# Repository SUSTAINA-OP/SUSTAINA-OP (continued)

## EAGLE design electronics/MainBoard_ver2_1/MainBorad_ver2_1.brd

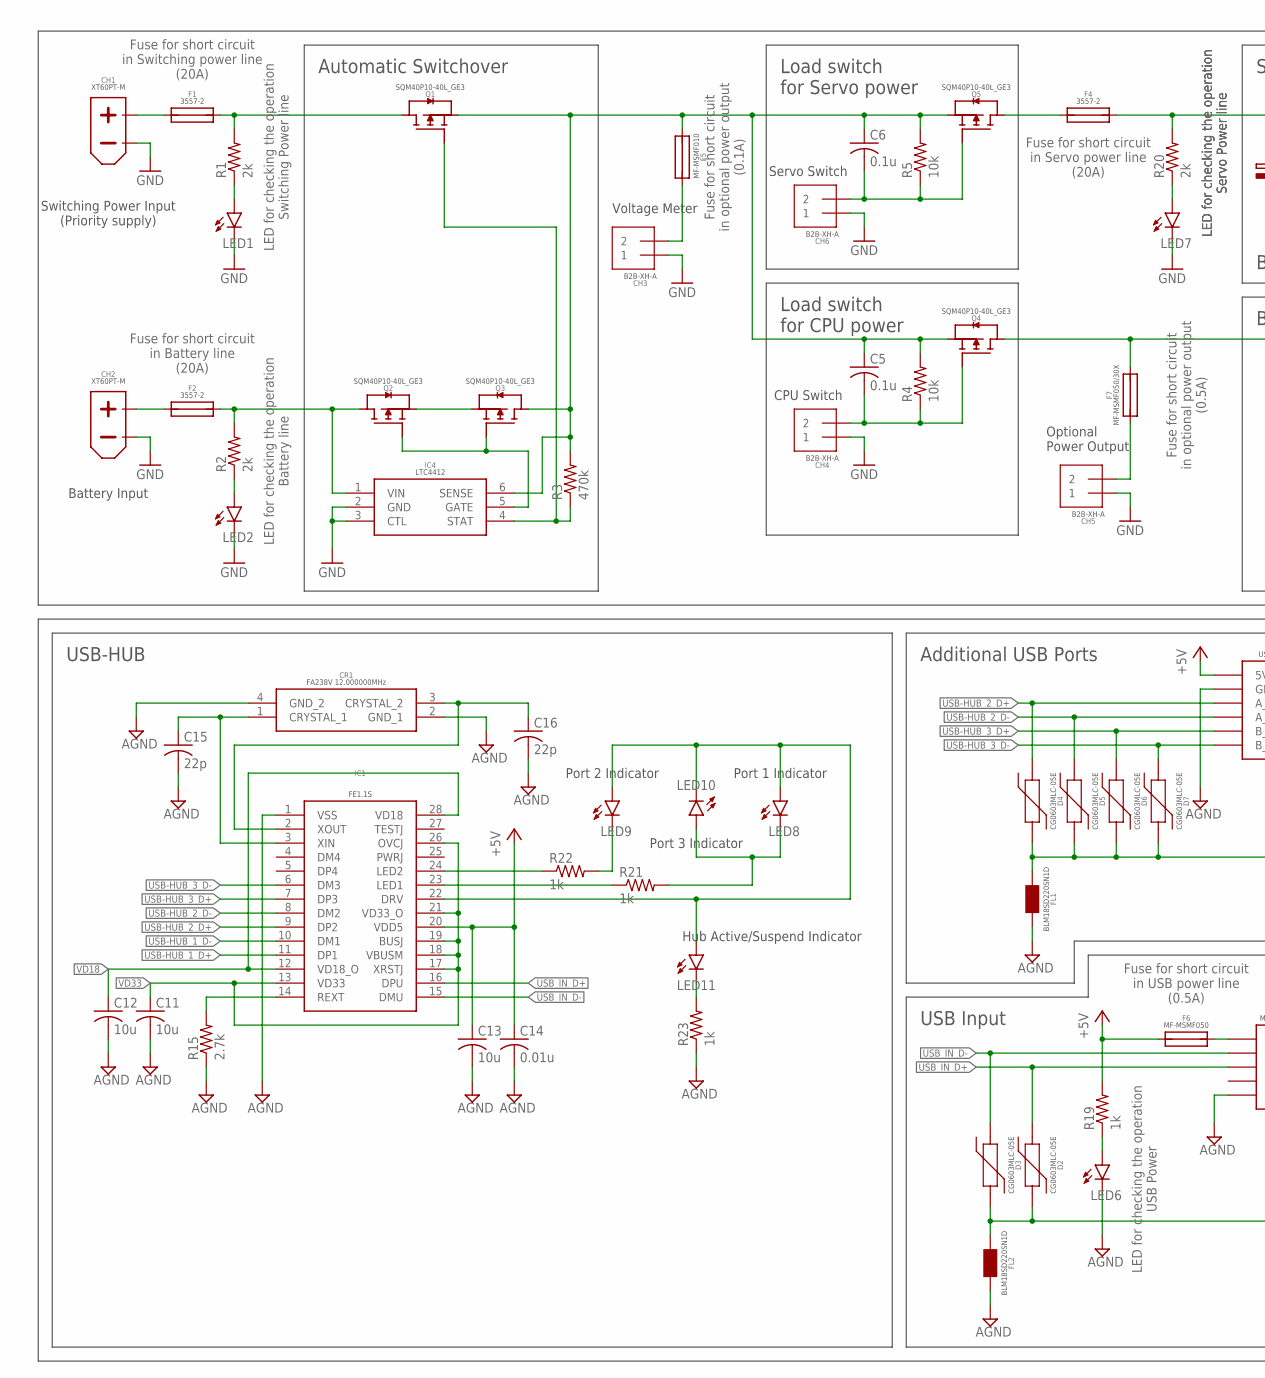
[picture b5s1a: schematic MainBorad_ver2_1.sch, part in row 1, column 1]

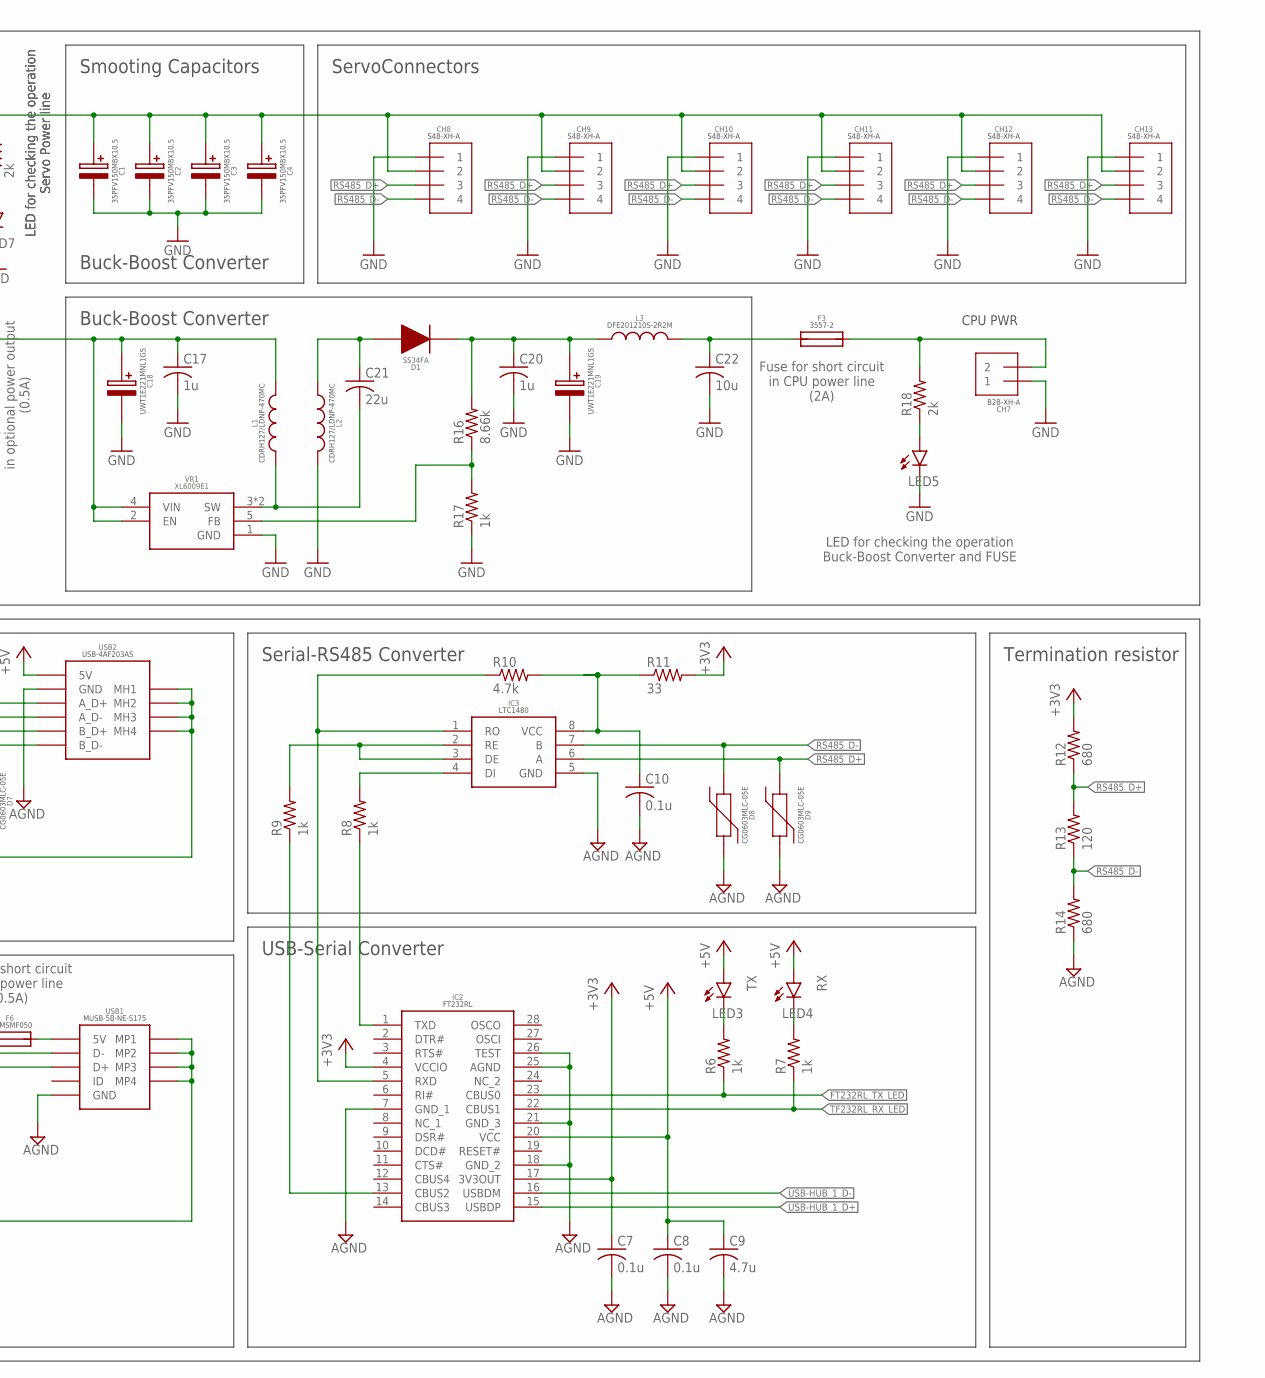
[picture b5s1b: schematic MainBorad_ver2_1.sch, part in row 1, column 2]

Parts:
C1, C2, C3, C4: 35PFV150M8X10.5
C5, C6, C7, C8, C10: 0.1u; C0603
C9: 4.7u; C0603
C11, C12, C13, C22: 10u; C0603
C14: 0.01u; C0603
C15, C16: 22p; C0603
C17, C20: 1u; C0603
C18, C19: UWT1E221MNL1GS
C21: 22u; C2012
CH1, CH2: XT60PT-M
CH3, CH4, CH5, CH6, CH7: B2B-XH-A
CH8, CH9, CH10, CH11, CH12, CH13: S4B-XH-A
CR1: FA238V_12.000000MHZ; FA238V
D1: SS34FA
D2, D3, D4, D5, D6, D7, D8, D9: CG0603MLC-05E
F1, F2, F3, F4: 3557-2
F5: MF-MSMF010
F6: MF-MSMF050
F7: MF-MSMF050/30X; MF-MSMF050
FL1, FL2: BLM18SD220SN1D
IC1: FE1.1S
IC2: FT232RL
IC3: LTC1480
IC4: LTC4412
L1, L2: CDRH127/LDNP-470MC; CDRH127/LDNP
L3: DFE201210S-2R2M; DFE201210S
LED1, LED2, LED3, LED4, LED5, LED6, LED7, LED8, LED9, LED10, LED11: LEDSML0603; SML0603
Q1, Q2, Q3, Q4, Q5: SQM40P10-40L_GE3; TO-252-3
R1, R2, R18, R20: 2k; R0603
R3: 470k; R0603
R4, R5: 10k; R0603
R6, R7, R8, R9, R17, R19, R21, R22, R23: 1k; R0603
R10: 4.7k; R0603
R11: 33; R0603
R12, R14: 680; R0603
R13: 120; R0603
R15: 2.7k; R0603
R16: 8.66k; R0603
USB1: MINI_USB_5P_B_TYPE
USB2: USB_4P_A_TYPE_X2
VR1: XL6009E1; TO263-5L

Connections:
+3V3: C7.1, IC2.4 (VCCIO), IC2.17 (3V3OUT), R11.2, R12.2
+5V: C8.1, C9.1, C13.1, C14.1, F6.1, IC1.20 (VDD5), IC2.20 (VCC), LED3.A, LED4.A, R19.2, USB2.4 (5V), USB2.8 (5V)
AGND: C7.2, C8.2, C9.2, C10.2, C11.2, C12.2, C13.2, C14.2, C15.2, C16.2, CR1.2 (GND_1), CR1.4 (GND_2), D8.2, D9.2, FL1.2, FL2.2, IC1.1 (VSS), IC2.7 (GND_1), IC2.18 (GND_2), IC2.21 (GND_3), IC2.25 (AGND), IC2.26 (TEST), IC3.5 (GND), LED6.C, R14.1, R15.1, R23.1, USB1.5 (GND), USB2.1 (GND), USB2.5 (GND)
A_DIODE_DCDC: C19.+, C20.1, D1.1, L3.1, R16.2
A_FUSE_BATT: F2.3 (2), F2.4 (2), IC4.1 (VIN), Q2.4 (D), R2.2
A_FUSE_DCDC: CH7.2, F3.3 (2), F3.4 (2), R18.2
A_FUSE_METER: CH3.2, F5.2
A_FUSE_PWR: F1.3 (2), F1.4 (2), Q1.4 (D), R1.2
A_FUSE_SERVO: C1.+, C2.+, C3.+, C4.+, CH8.2, CH9.2, CH10.2, CH11.2, CH12.2, CH13.2, F4.3 (2), F4.4 (2), R20.2
B_DIODE_DCDC: C21.1, D1.2, L2.1
B_FUSE_BATT: CH2.+, F2.1, F2.2 (1)
B_FUSE_DCDC: C22.1, F3.1, F3.2 (1), L3.2
B_FUSE_PWR: CH1.+, F1.1, F1.2 (1)
B_FUSE_SERVO: F4.1, F4.2 (1), Q5.4 (D)
B_FUSE_USB_MINI_B: F6.2, USB1.1 (5V)
B_LOAD_CPU: C5.2, CH4.2, Q4.1 (G), R4.1
B_LOAD_SERVO: C6.2, CH6.2, Q5.1 (G), R5.1
CPU_PWR_IN: C17.1, C18.+, F7.2, L1.2, Q4.4 (D), VR1.2 (EN), VR1.4 (VIN)
EN: IC3.2 (RE), IC3.3 (DE), R9.2
FB_DCDC: R16.1, R17.2, VR1.5 (FB)
FE1.1S_DRV: IC1.22 (DRV), LED8.A, LED9.A, LED10.C, LED11.A
FE1.1S_DRV_LED_A: LED11.C, R23.2
FE1.1S_LED1_A: LED8.C, LED10.A, R21.2
FE1.1S_LED_1_B: IC1.23 (LED1), R21.1
FE1.1S_LED_2_A: LED9.C, R22.2
FE1.1S_LED_2_B: IC1.24 (LED2), R22.1
FT232RL_CBUS2: IC2.13 (CBUS2), R9.1
FT232RL_RXD: IC2.5 (RXD), IC3.1 (RO), R10.1
FT232RL_TXD: IC2.1 (TXD), R8.1
FT232RL_TX_LED: IC2.23 (CBUS0), R6.1
GND: C1.-, C2.-, C3.-, C4.-, C17.2, C18.-, C19.-, C20.2, C22.2, CH1.-, CH2.-, CH3.1, CH4.1, CH5.1, CH6.1, CH7.1, CH8.1, CH9.1, CH10.1, CH11.1, CH12.1, CH13.1, IC4.2 (GND), IC4.3 (CTL), L2.2, LED1.C, LED2.C, LED5.C, LED7.C, R17.1, VR1.1 (GND)
INPUT_PWR: C5.1, C6.1, F5.1, IC4.6 (SENSE), Q1.3 (S), Q3.4 (D), Q4.3 (S), Q5.3 (S), R3.2, R4.2, R5.2
LED_BATT: LED2.A, R2.1
LED_DCDCOUT: LED5.A, R18.1
LED_FT232RL_RX: LED4.C, R7.2
LED_FT232RL_TX: LED3.C, R6.2
LED_PWR: LED1.A, R1.1
LED_SERVO: LED7.A, R20.1
LED_USBIN: LED6.A, R19.1
LTC1480_DI: IC3.4 (DI), R8.2
LTC1480_VCC: C10.1, IC3.8 (VCC), R10.2, R11.1
LTC4412_GATE: IC4.5 (GATE), Q2.1 (G), Q3.1 (G)
LTC4412_STAT: IC4.4 (STAT), Q1.1 (G), R3.1
POWER_OUTPUT: CH5.2, F7.1
REXT_FE1.1S: IC1.14 (REXT), R15.2
RS485_D+: CH8.3, CH9.3, CH10.3, CH11.3, CH12.3, CH13.3, D9.1, IC3.6 (A), R12.1, R13.2
RS485_D-: CH8.4, CH9.4, CH10.4, CH11.4, CH12.4, CH13.4, D8.1, IC3.7 (B), R13.1, R14.2
SOURCE: Q2.3 (S), Q3.3 (S)
SW_DCDC: C21.2, L1.1, VR1.3 (SW), VR1.6 (SW)
TF232RL_RX_LED: IC2.22 (CBUS1), R7.1
USB-HUB_1_D+: IC1.11 (DP1), IC2.15 (USBDP)
USB-HUB_1_D-: IC1.10 (DM1), IC2.16 (USBDM)
USB-HUB_2_D+: D4.1, IC1.9 (DP2), USB2.2 (A_D+)
USB-HUB_2_D-: D5.1, IC1.8 (DM2), USB2.3 (A_D-)
USB-HUB_3_D+: D6.1, IC1.7 (DP3), USB2.6 (B_D+)
USB-HUB_3_D-: D7.1, IC1.6 (DM3), USB2.7 (B_D-)
USB_A_SHIELD: D4.2, D5.2, D6.2, D7.2, FL1.1, USB2.MH1, USB2.MH2, USB2.MH3, USB2.MH4
USB_IN_D+: D2.1, IC1.16 (DPU), USB1.3 (D+)
USB_IN_D-: D3.1, IC1.15 (DMU), USB1.2 (D-)
USB_MINI_B_SHIELD: D2.2, D3.2, FL2.1, USB1.MP1, USB1.MP2, USB1.MP3, USB1.MP4
VD18: C12.1, IC1.12 (VD18_O), IC1.28 (VD18)
VD33: C11.1, IC1.13 (VD33), IC1.17 (XRSTJ), IC1.18 (VBUSM), IC1.19 (BUSJ), IC1.21 (VD33_O), IC1.26 (OVCJ)
XIN_FE1.1S: C15.1, CR1.1 (CRYSTAL_1), IC1.3 (XIN)
XOUT_FE1.1S: C16.1, CR1.3 (CRYSTAL_2), IC1.2 (XOUT)

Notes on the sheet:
Hub Active/Suspend Indicator
Port 1 Indicator
Port 2 Indicator
Port 3 Indicator
CPU Switch
Battery Input
Switching Power Input (Priority supply)
Servo Switch
Voltage Meter
Optional Power Output
ServoConnectors
Buck-Boost Converter
Smooting Capacitors
Termination resistor
USB-HUB
Additional USB Ports
USB Input
LED for checking the operation Buck-Boost Converter and FUSE
Fuse for short circuit in CPU power line (2A)
CPU PWR
Fuse for short circuit in Servo power line (20A)
Load switch for Servo power
Load switch for CPU power
Fuse for short circuit in optional power output (0.5A)
Automatic Switchover
Fuse for short circuit in Switching power line (20A)
Fuse for short circuit in Battery line (20A)
LED for checking the operation Switching Power line
LED for checking the operation Battery line
Fuse for short circuit in optional power output (0.1A)
Fuse for short circuit in USB power line (0.5A)
LED for checking the operation Servo Power line
Serial-RS485 Converter
USB-Serial Converter
LED for checking the operation USB Power

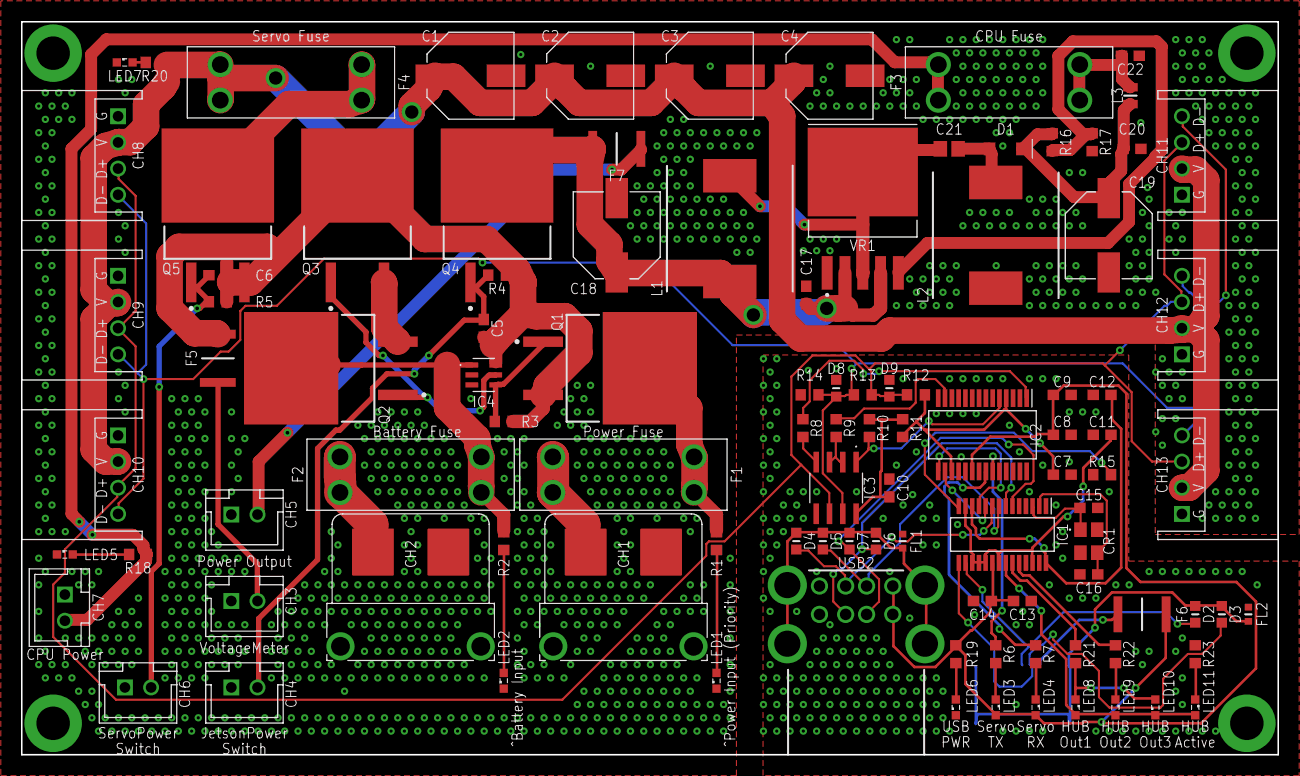
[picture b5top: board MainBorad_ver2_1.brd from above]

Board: 2 copper layers, 120.0 x 70.0 mm, 103 parts (1 on the bottom side), 64 nets.

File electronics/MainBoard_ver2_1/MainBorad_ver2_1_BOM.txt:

Partlist exported from C:/Users/Masato/Desktop/Ver2.1/MainBorad_ver2_1.sch at 2022/02/20 3:17

Qty Value               Device              Package            Parts                                                              Description                POPULARITY SPICEPREFIX
11                      LEDSML0603          SML0603            LED1, LED2, LED3, LED4, LED5, LED6, LED7, LED8, LED9, LED10, LED11 LED                        17                    
1   0.01u               C-USC0603           C0603              C14                                                                CAPACITOR, American symbol 37         C          
5   0.1u                C-USC0603           C0603              C5, C6, C7, C8, C10                                                CAPACITOR, American symbol 37         C          
2   10k                 R-US_R0603          R0603              R4, R5                                                             RESISTOR, American symbol  77         R          
4   10u                 C-USC0603           C0603              C11, C12, C13, C22                                                 CAPACITOR, American symbol 37         C          
1   120                 R-US_R0603          R0603              R13                                                                RESISTOR, American symbol  77         R          
9   1k                  R-US_R0603          R0603              R6, R7, R8, R9, R17, R19, R21, R22, R23                            RESISTOR, American symbol  77         R          
2   1u                  C-USC0603           C0603              C17, C20                                                           CAPACITOR, American symbol 37         C          
1   2.7k                R-US_R0603          R0603              R15                                                                RESISTOR, American symbol  77         R          
2   22p                 C-USC0603           C0603              C15, C16                                                           CAPACITOR, American symbol 37         C          
1   22u                 C-USC2012           C2012              C21                                                                CAPACITOR, American symbol 0          C          
4   2k                  R-US_R0603          R0603              R1, R2, R18, R20                                                   RESISTOR, American symbol  77         R          
1   33                  R-US_R0603          R0603              R11                                                                RESISTOR, American symbol  77         R          
4   3557-2              3557-2              3557-2             F1, F2, F3, F4                                                                                                      
4   35PFV150M8X10.5     35PFV150M8X10.5     35PFV150M8X10.5    C1, C2, C3, C4                                                                                                      
1   4.7k                R-US_R0603          R0603              R10                                                                RESISTOR, American symbol  77         R          
1   4.7u                C-USC0603           C0603              C9                                                                 CAPACITOR, American symbol 37         C          
1   470k                R-US_R0603          R0603              R3                                                                 RESISTOR, American symbol  77         R          
2   680                 R-US_R0603          R0603              R12, R14                                                           RESISTOR, American symbol  77         R          
1   8.66k               R-US_R0603          R0603              R16                                                                RESISTOR, American symbol  77         R          
5   B2B-XH-A            B2B-XH-A            B2B-XH-A           CH3, CH4, CH5, CH6, CH7                                                                                             
2   BLM18SD220SN1D      BLM18SD220SN1D      BLM18SD220SN1D     FL1, FL2                                                                                                            
2   CDRH127/LDNP-470MC  CDRH127/LDNP-470MC  CDRH127/LDNP       L1, L2                                                                                                              
8   CG0603MLC-05E       CG0603MLC-05E       CG0603MLC-05E      D2, D3, D4, D5, D6, D7, D8, D9                                                                                      
1   DFE201210S-2R2M     DFE201210S-2R2M     DFE201210S         L3                                                                                                                  
1   FA238V_12.000000MHZ FA238V_12.000000MHZ FA238V             CR1                                                                                                                 
1   FE1.1S              FE1.1S              FE1.1S             IC1                                                                                                                 
1   FT232RL             FT232RL             FT232RL            IC2                                                                                                                 
1   LTC1480             LTC1480             LTC1480            IC3                                                                                                                 
1   LTC4412             LTC4412             LTC4412            IC4                                                                                                                 
1   MF-MSMF010          MF-MSMF010          MF-MSMF010         F5                                                                                                                  
1   MF-MSMF050          MF-MSMF050          MF-MSMF050         F6                                                                                                                  
1   MF-MSMF050/30X      MF-MSMF050/30X      MF-MSMF050         F7                                                                                                                  
1   MINI_USB_5P_B_TYPE  MINI_USB_5P_B_TYPE  MINI_USB_5P_B_TYPE USB1                                                                                                                
6   S4B-XH-A            S4B-XH-A            S4B-XH-A           CH8, CH9, CH10, CH11, CH12, CH13                                                                                    
5   SQM40P10-40L_GE3    SQM40P10-40L_GE3    TO-252-3           Q1, Q2, Q3, Q4, Q5                                                                                                  
1   SS34FA              SS34FA              SS34FA             D1                                                                                                                  
1   USB_4P_A_TYPE_X2    USB_4P_A_TYPE_X2    USB_4P_A_TYPE_X2   USB2                                                                                                                
2   UWT1E221MNL1GS      UWT1E221MNL1GS      UWT1E221MNL1GS     C18, C19                                                                                                            
1   XL6009E1            XL6009E1            TO263-5L           VR1                                                                                                                 
2   XT60PT-M            XT60PT-M            XT60PT-M           CH1, CH2

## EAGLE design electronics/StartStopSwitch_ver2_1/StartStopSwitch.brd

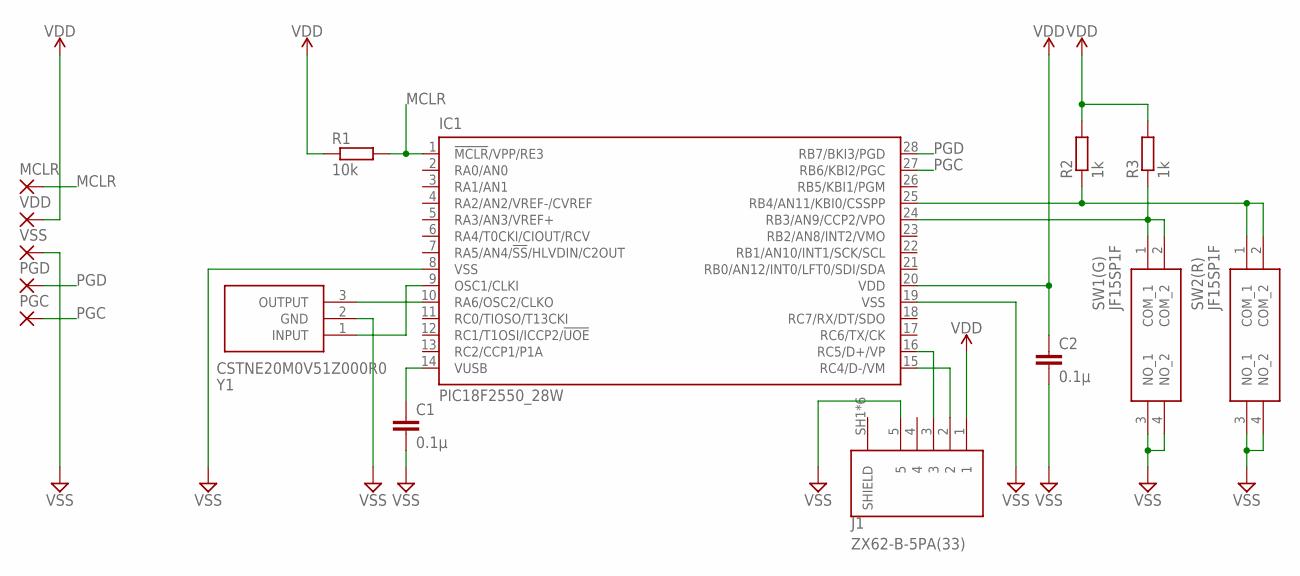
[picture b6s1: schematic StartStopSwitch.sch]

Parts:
C1: 0.1μ; C0603
C2: 0.1µ; C0603
IC1: PIC18F2550_28W; SO28W
J1: ZX62-B-5PA(33); HRS_ZX62-B-5PA(33)
MCLR: 1,6/0,8
PGC: 1,6/0,8
PGD: 1,6/0,8
R1: 10k; R0603
R2, R3: 1k; R0603
SW1(G), SW2(R): JF15SP1F
VDD: 1,6/0,8
VSS: 1,6/0,8
Y1: CSTNE20M0V51Z000R0

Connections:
MCLR: IC1.1 (!MCLR!/VPP/RE3), MCLR.1, R1.2
unnamed: C1.1, IC1.14 (VUSB)
unnamed: IC1.10 (RA6/OSC2/CLKO), Y1.3 (OUTPUT)
unnamed: IC1.9 (OSC1/CLKI), Y1.1 (INPUT)
unnamed: IC1.24 (RB3/AN9/CCP2/VPO), R3.1, SW1(G).1 (COM_1), SW1(G).2 (COM_2)
unnamed: IC1.25 (RB4/AN11/KBI0/CSSPP), R2.1, SW2(R).1 (COM_1), SW2(R).2 (COM_2)
unnamed: IC1.15 (RC4/D-/VM), J1.2
unnamed: IC1.16 (RC5/D+/VP), J1.3
PGC: IC1.27 (RB6/KBI2/PGC), PGC.1
PGD: IC1.28 (RB7/BKI3/PGD), PGD.1
VDD: C2.1, IC1.20 (VDD), J1.1, R1.1, R2.2, R3.2, VDD.1
VSS: C1.2, C2.2, IC1.8 (VSS), IC1.19 (VSS), J1.5, SW1(G).3 (NO_1), SW1(G).4 (NO_2), SW2(R).3 (NO_1), SW2(R).4 (NO_2), VSS.1, Y1.2 (GND)

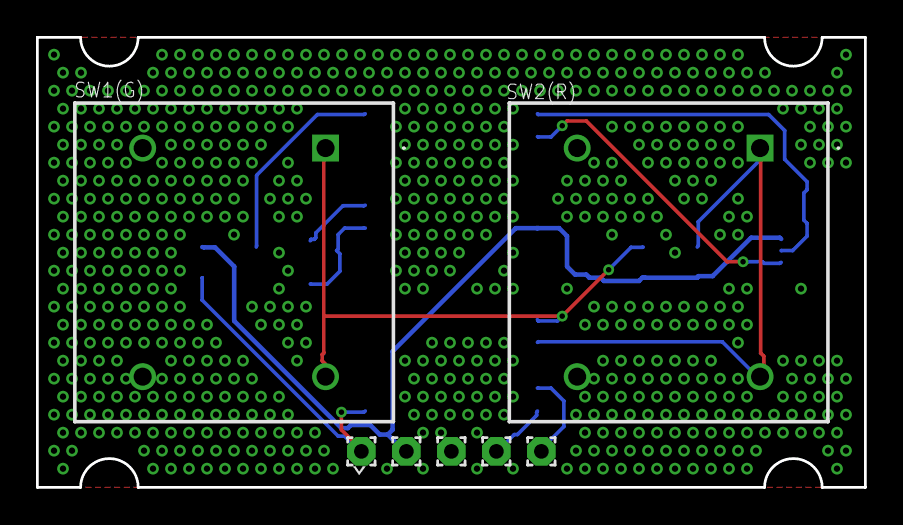
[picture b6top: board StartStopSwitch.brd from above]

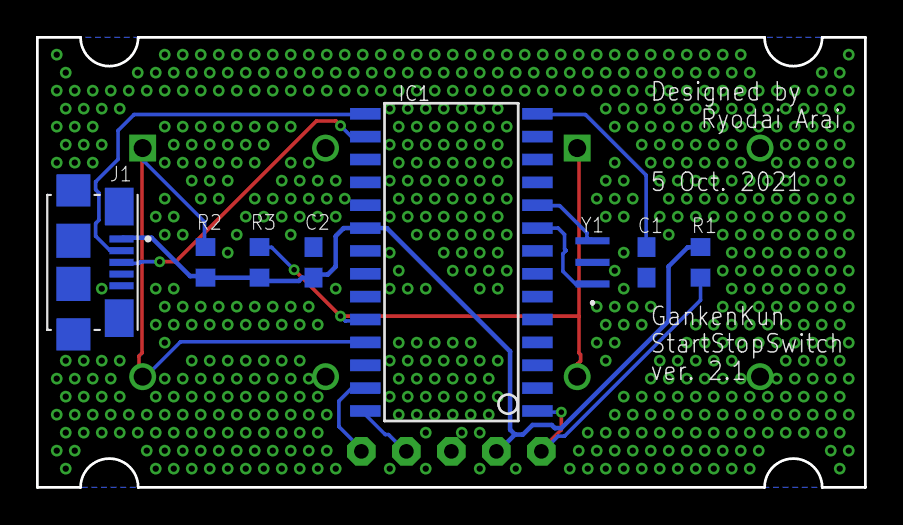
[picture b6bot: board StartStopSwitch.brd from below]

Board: 2 copper layers, 46.0 x 25.0 mm, 15 parts (8 on the bottom side), 12 nets.

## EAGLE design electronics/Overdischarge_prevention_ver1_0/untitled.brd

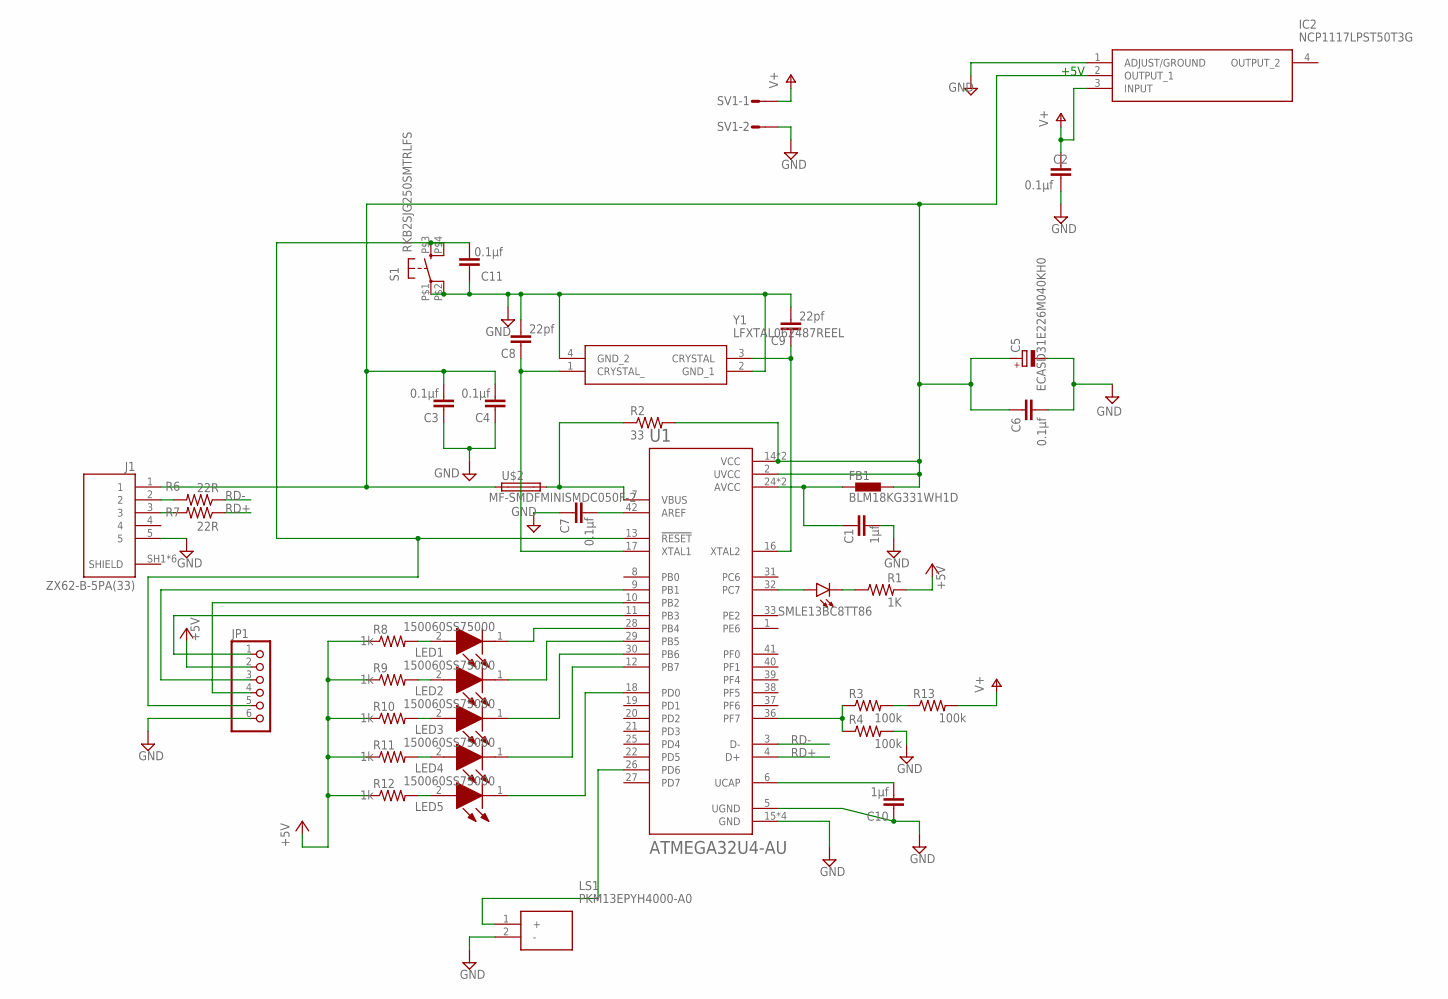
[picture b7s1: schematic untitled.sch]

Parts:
C1, C10: 1μf; C0603
C2, C3, C4, C6, C7, C11: 0.1μf; C0603
C5: ECASD31E226M040KH0
C8, C9: 22pf; C0603
FB1: BLM18KG331WH1D; BEADC1608X75N
IC2: NCP1117LPST50T3G; SOT230P700X180-4N
J1: ZX62-B-5PA(33); HRS_ZX62-B-5PA(33)
JP1: PINHD-1X6; 1X06
LD1: LEDCHIPLED_0603; CHIPLED_0603
LED1, LED2, LED3, LED4, LED5: 150060SS75000; LEDC1608X80N
LS1: PKM13EPYH4000-A0; PKM13EPYH4002-B0
R1: 1K; R0603
R2: 33; R0603
R3, R4, R13: 100k; R0603
R6, R7: 22R; R0603
R8, R9, R10, R11, R12: 1k; R0603
S1: RKB2SJG250SMTRLFS
SV1: L02P
U1: ATMEGA32U4-AU; QFP80P1200X1200X120-44N
U$2: MF-SMDFMINISMDC050F-2; MINISMDC050F-2
Y1: LFXTAL062487REEL

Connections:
+5V: JP1.2, R1.2, R8.1, R9.1, R10.1, R11.1, R12.1
GND: C1.2, C2.2, C3.1, C4.1, C5.P$2 (-), C6.1, C7.1, C8.2, C9.2, C10.1, C11.1, IC2.1 (ADJUST/GROUND), J1.5, JP1.6, LS1.2 (-), R4.2, S1.P$1, S1.P$2 (P1), SV1.2, U1.5 (UGND), U1.15 (GND), U1.23 (GND), U1.35 (GND), U1.43 (GND), Y1.2 (GND_1), Y1.4 (GND_2)
unnamed: C7.2, U1.42 (AREF)
unnamed: C10.2, U1.6 (UCAP)
unnamed: C1.1, FB1.1, U1.24 (AVCC), U1.44 (AVCC)
unnamed: LD1.A, U1.32 (PC7)
unnamed: C8.1, U1.17 (XTAL1), Y1.1 (CRYSTAL_)
unnamed: C9.1, U1.16 (XTAL2), Y1.3 (CRYSTAL)
unnamed: LED5.1 (K), U1.18 (PD0)
unnamed: C3.2, C4.2, C5.P$1 (+), C6.2, FB1.2, IC2.2 (OUTPUT_1), J1.1, R2.2, U1.2 (UVCC), U1.14 (VCC), U1.34 (VCC), U$2.P$1 (1)
unnamed: J1.2, R6.2
unnamed: J1.3, R7.2
unnamed: LD1.C, R1.1
unnamed: R3.1, R4.1, U1.36 (PF7)
unnamed: R3.2, R13.1
unnamed: R2.1, U1.7 (VBUS), U$2.P$2 (2)
unnamed: JP1.1, U1.11 (PB3)
unnamed: JP1.3, U1.9 (PB1)
unnamed: JP1.4, U1.10 (PB2)
unnamed: LED4.1 (K), U1.12 (PB7)
unnamed: LED3.1 (K), U1.30 (PB6)
unnamed: C11.2, JP1.5, S1.P$3 (S), S1.P$4 (S1), U1.13 (!RESET)
unnamed: LED2.1 (K), U1.29 (PB5)
unnamed: LED1.1 (K), U1.28 (PB4)
unnamed: LED1.2 (A), R8.2
unnamed: LED2.2 (A), R9.2
unnamed: LED3.2 (A), R10.2
unnamed: LED4.2 (A), R11.2
unnamed: LED5.2 (A), R12.2
unnamed: LS1.1 (+), U1.26 (PD6)
RD+: R7.1, U1.4 (D+)
RD-: R6.1, U1.3 (D-)
V+: C2.1, IC2.3 (INPUT), R13.2, SV1.1

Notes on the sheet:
+5V
SMLE13BC8TT86

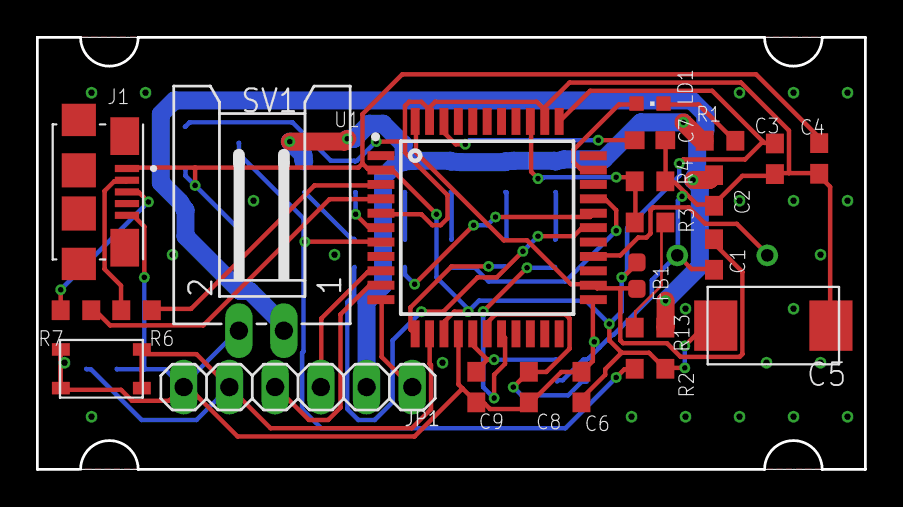
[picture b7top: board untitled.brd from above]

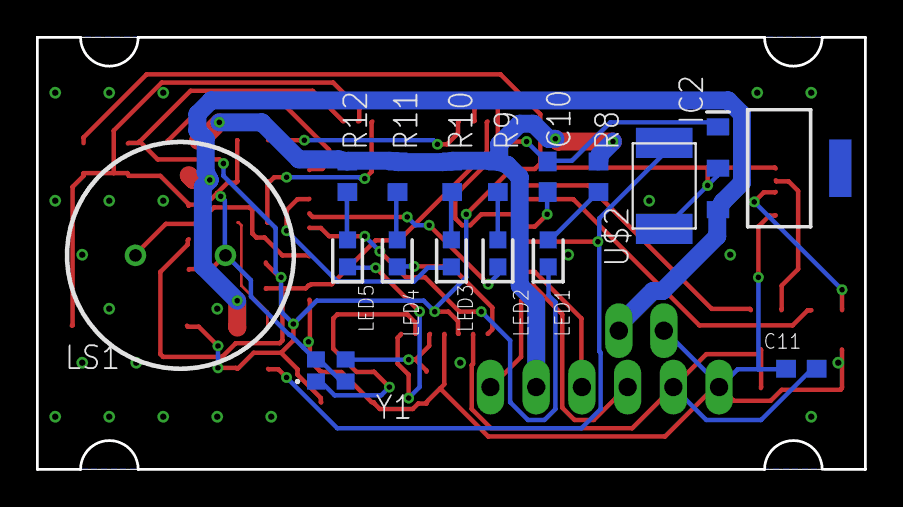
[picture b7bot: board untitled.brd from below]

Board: 2 copper layers, 46.0 x 24.0 mm, 39 parts (16 on the bottom side), 33 nets.

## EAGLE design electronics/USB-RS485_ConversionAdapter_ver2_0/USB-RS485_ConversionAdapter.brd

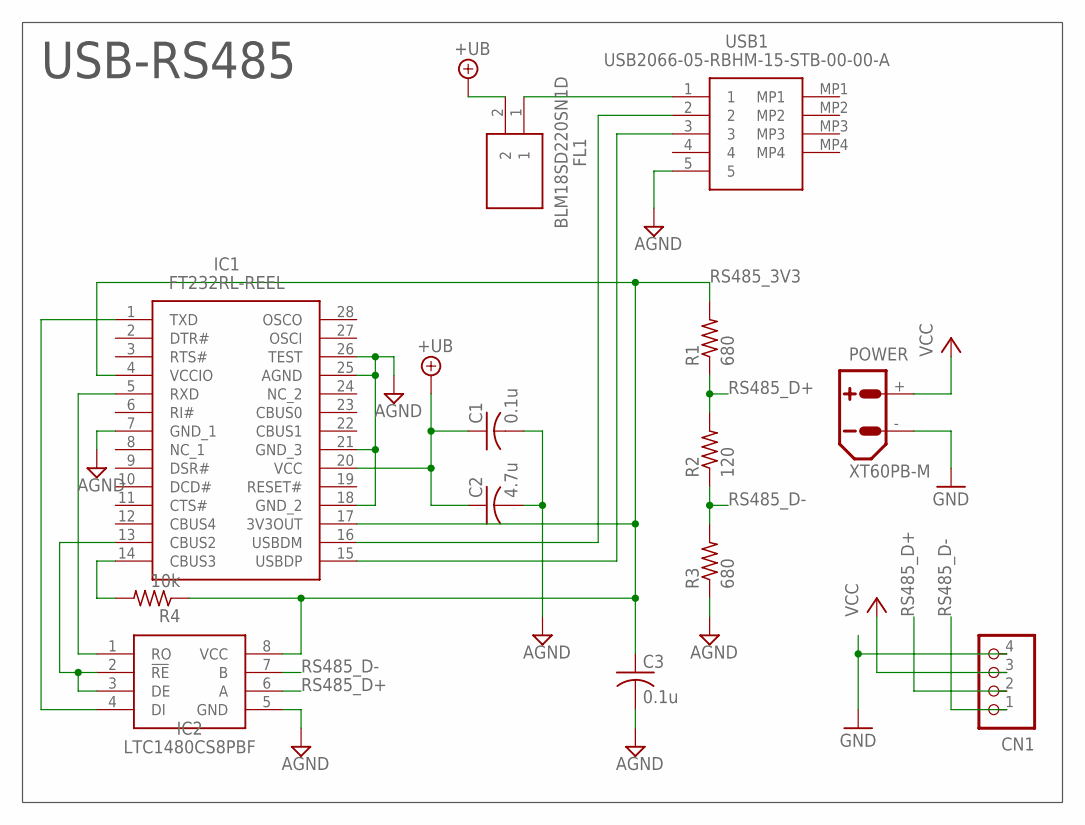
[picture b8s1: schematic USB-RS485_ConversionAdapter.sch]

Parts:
C1, C3: 0.1u; C1608
C2: 4.7u; C1608
CN1: B4B-XH-A
FL1: BLM18SD220SN1D; BLM18AG102BH1D
IC1: FT232RL-REEL; SOP65P778X200-28N
IC2: LTC1480CS8PBF; SOIC127P599X175-8N
POWER: XT60PB-M
R1, R3: 680; R0603
R2: 120; R0603
R4: 10k; R0603
USB1: USB2066-05-RBHM-15-STB-00-00-A; USB206605RBHM15STB0000A

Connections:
+UB: C1.1, C2.1, FL1.2, IC1.20 (VCC)
AGND: C1.2, C2.2, C3.2, IC1.7 (GND_1), IC1.18 (GND_2), IC1.21 (GND_3), IC1.25 (AGND), IC1.26 (TEST), IC2.5 (GND), R3.1, USB1.5
GND: CN1.4, POWER.-
RS485_1: IC1.14 (CBUS3), R4.2
RS485_2: IC1.13 (CBUS2), IC2.2 (!RE), IC2.3 (DE)
RS485_3V3: C3.1, IC1.4 (VCCIO), IC1.17 (3V3OUT), IC2.8 (VCC), R1.2, R4.1
RS485_D+: CN1.2, IC2.6 (A), R1.1, R2.2
RS485_D-: CN1.1, IC2.7 (B), R2.1, R3.2
RXD: IC1.5 (RXD), IC2.1 (RO)
TXD: IC1.1 (TXD), IC2.4 (DI)
USB_5V: FL1.1, USB1.1
USB_D+: IC1.15 (USBDP), USB1.3
USB_D-: IC1.16 (USBDM), USB1.2
VCC: CN1.3, POWER.+

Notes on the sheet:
USB-RS485

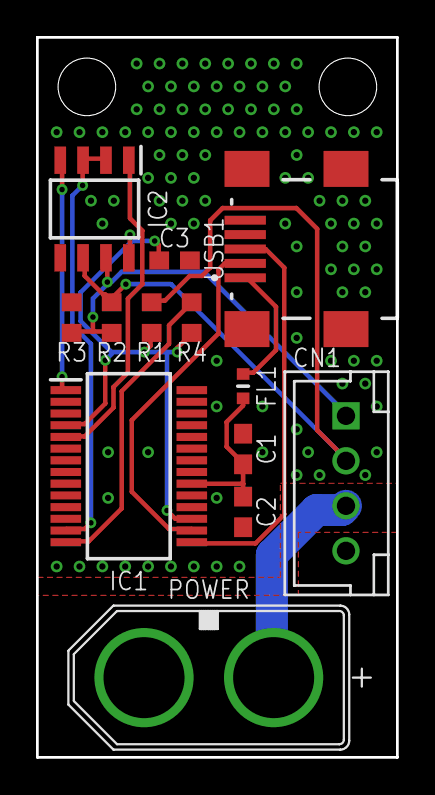
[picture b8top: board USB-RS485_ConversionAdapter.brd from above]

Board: 2 copper layers, 20.0 x 40.0 mm, 13 parts (0 on the bottom side), 14 nets.
